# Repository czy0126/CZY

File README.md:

# CZY — 48 V → 约 2 V 薄型固定变比 DCX

**D1 当前设计目标：** 约 24:1 固定比、100 A 输出目标、整机高度 ≤16 mm；成本暂不限制。D2 的 120 A 与 D3 的 ≤10 mm 均后置，保护、绝缘、载流与制造签核不可省。

> **当前研发分支：[`feat/d1-fab-package`](https://github.com/czy0126/CZY/tree/feat/d1-fab-package)。默认 `main` 仍是历史快照。当前 D1 为 `NOT_FOR_FAB`；真实样机尚未获得投板或额定许可。**

## 从这里开始（不用翻旧审核报告）

1. **[D1 当前交接面板](docs/D1_CURRENT.md)**：唯一当前可编辑 G1 原生 PCB、已发生的 ECO、三条并行任务及下一次操作/验收。
2. **[D1 已决事项与重开条件](docs/D1_DECISIONS.md)**：R8/R6、Lr XY、九根布线预检、100 A 铜路等已经确认的边界；禁止重复审查同一证据。
3. **[第49章：D1 G1→G2→G3 交付合同](docs/D1_EXECUTION_KIT/49_D1主功率板PCB唯一执行计划_2026-11-09.md)**：阶段目标、冻结条件与实际制造要求；其 11/9 日期快照不覆盖当前 G1 读回。
4. **[历史技术资料索引](docs/D1_REFERENCE_INDEX.md)**：资料在哪里、哪些只作参考。原 README 的长篇历史更新已[归档](docs/archive/README_D1_branch_before_single_entry_2026-11-10.md)，保留所有技术原文和链接。

**唯一任务入口：** [Issue #4 总交付](https://github.com/czy0126/CZY/issues/4)，以及 [#9 原生 PCB/器件](https://github.com/czy0126/CZY/issues/9)、[#12 磁件与接口](https://github.com/czy0126/CZY/issues/12)、[#36 D0 保护](https://github.com/czy0126/CZY/issues/36)。**同时最多 A/B/C 三个工程工作包**；不为“再次审核/继续优化”新建总计划。

## 实际应该先做什么

**A 线优先：** 9条控制小信号增量已完成原生重开验收，未连接206→199，Physical 0、Netlist仍1；见[同CAD审核回执](hardware/dcx_main/g1/lr_signal_review_report.json)。下一步处理原生Import Changes逐位号差异、实体Cout和100 A两极铜路，不重复重画已有短线。

```powershell
python -m pytest tools/test_g1_copper_coverage.py tools/test_g1_driver_route_plan.py -q
```

上述测试是回归检查，不替代原生DRC；本轮信号候选及失败回执全部保留，尚待随本轮提交提升基线。B（真实 Maxwell/实体 PAD）与 C（D0 真实关断）并行，不得以模拟或脚本绿色替代实际硬件证据。

**工程和开发规则：** [`CLAUDE.md`](CLAUDE.md) · [`docs/agent/EDA.md`](docs/agent/EDA.md) · [PR 模板](.github/PULL_REQUEST_TEMPLATE.md)。任何 PR 应说明真实产物的**改动前后、原始证据和下一次实际交付**。仅更换“最新计划”标题或重复风险总结不算里程碑。

**制造许可唯一来源：** [`hardware/dcx_main/d1_fabrication_gate.json`](hardware/dcx_main/d1_fabrication_gate.json) 及其相同 CAD 修订版的独立审核证据；历史 JSON 不能混用为 G1 的签核。

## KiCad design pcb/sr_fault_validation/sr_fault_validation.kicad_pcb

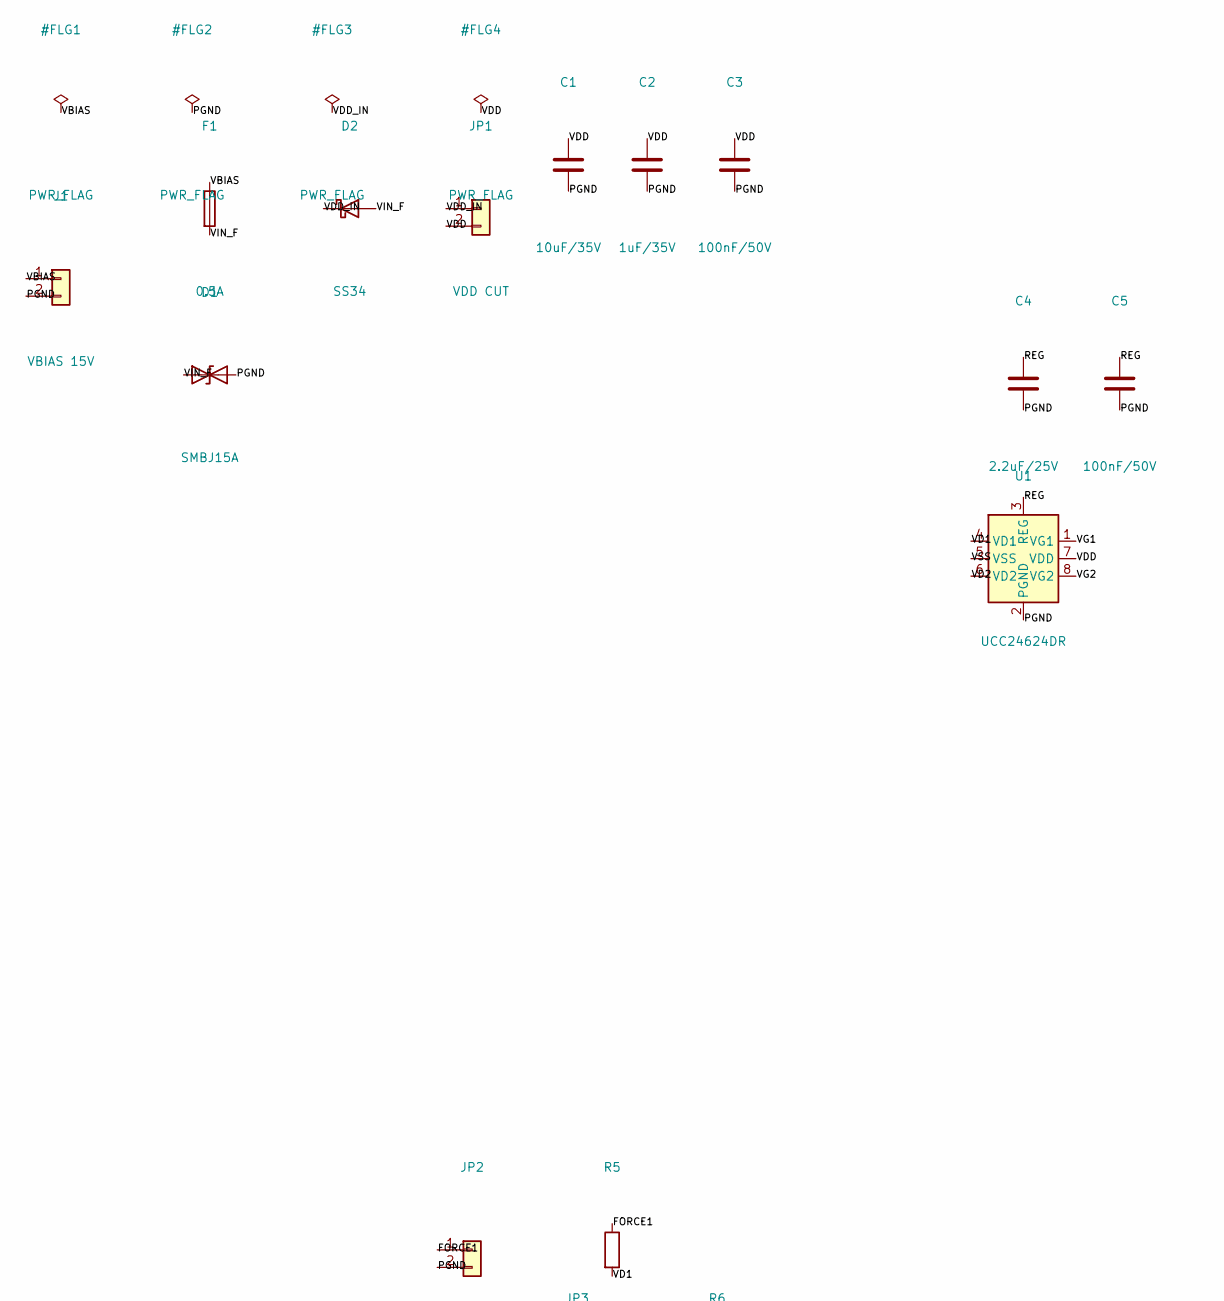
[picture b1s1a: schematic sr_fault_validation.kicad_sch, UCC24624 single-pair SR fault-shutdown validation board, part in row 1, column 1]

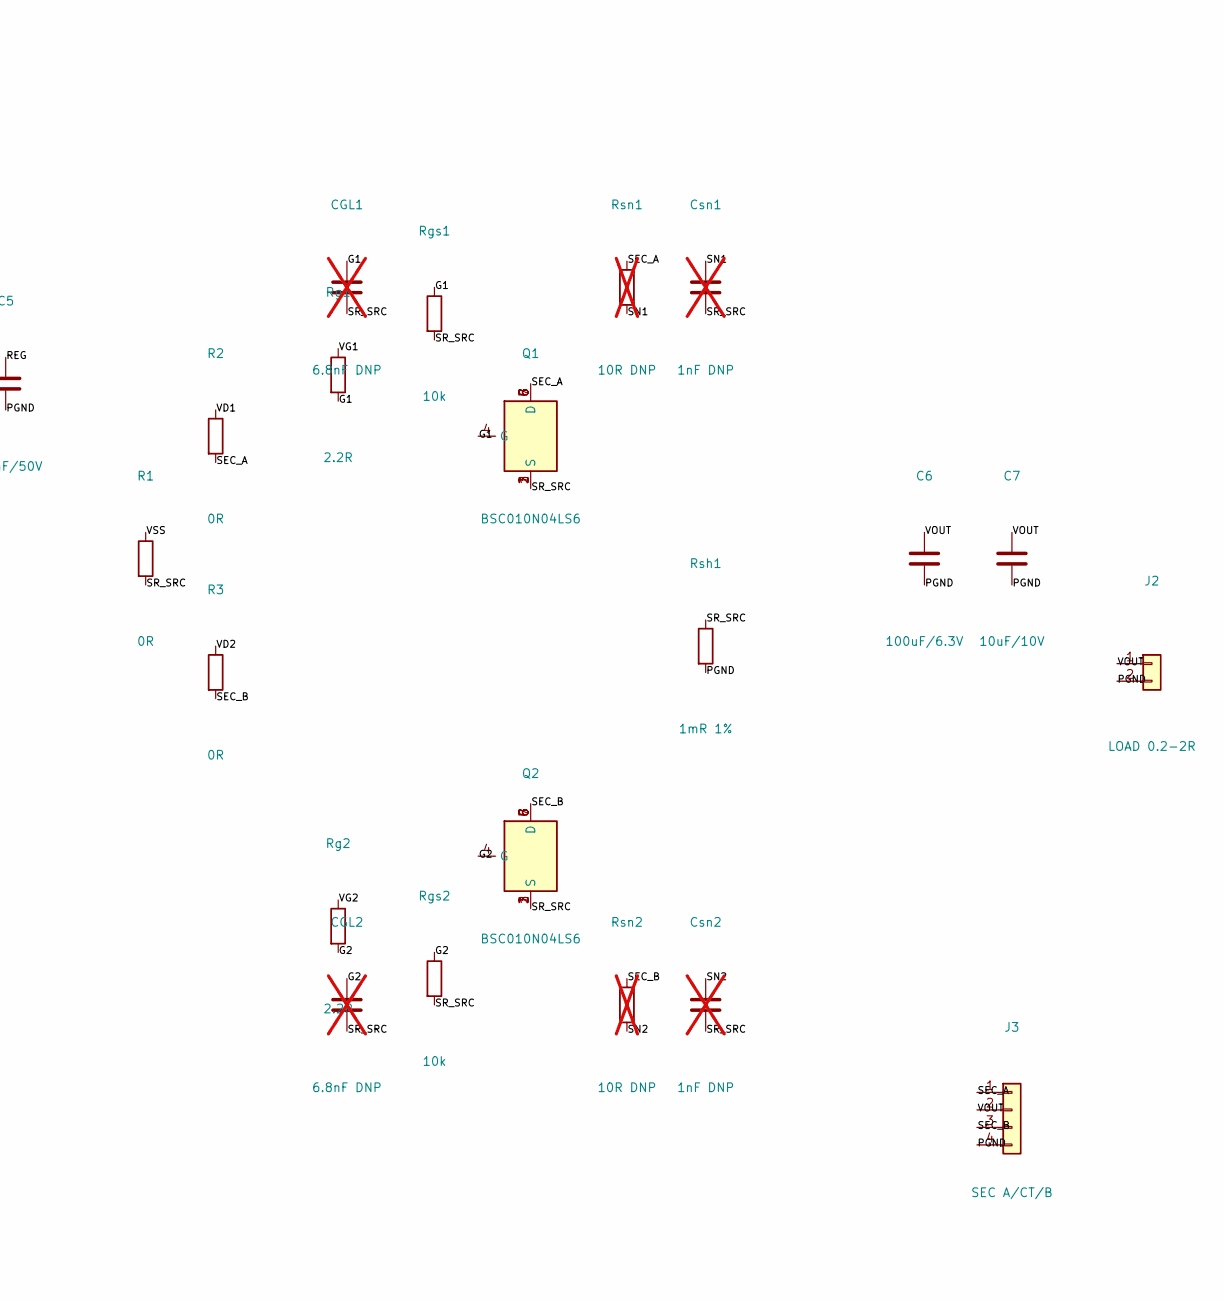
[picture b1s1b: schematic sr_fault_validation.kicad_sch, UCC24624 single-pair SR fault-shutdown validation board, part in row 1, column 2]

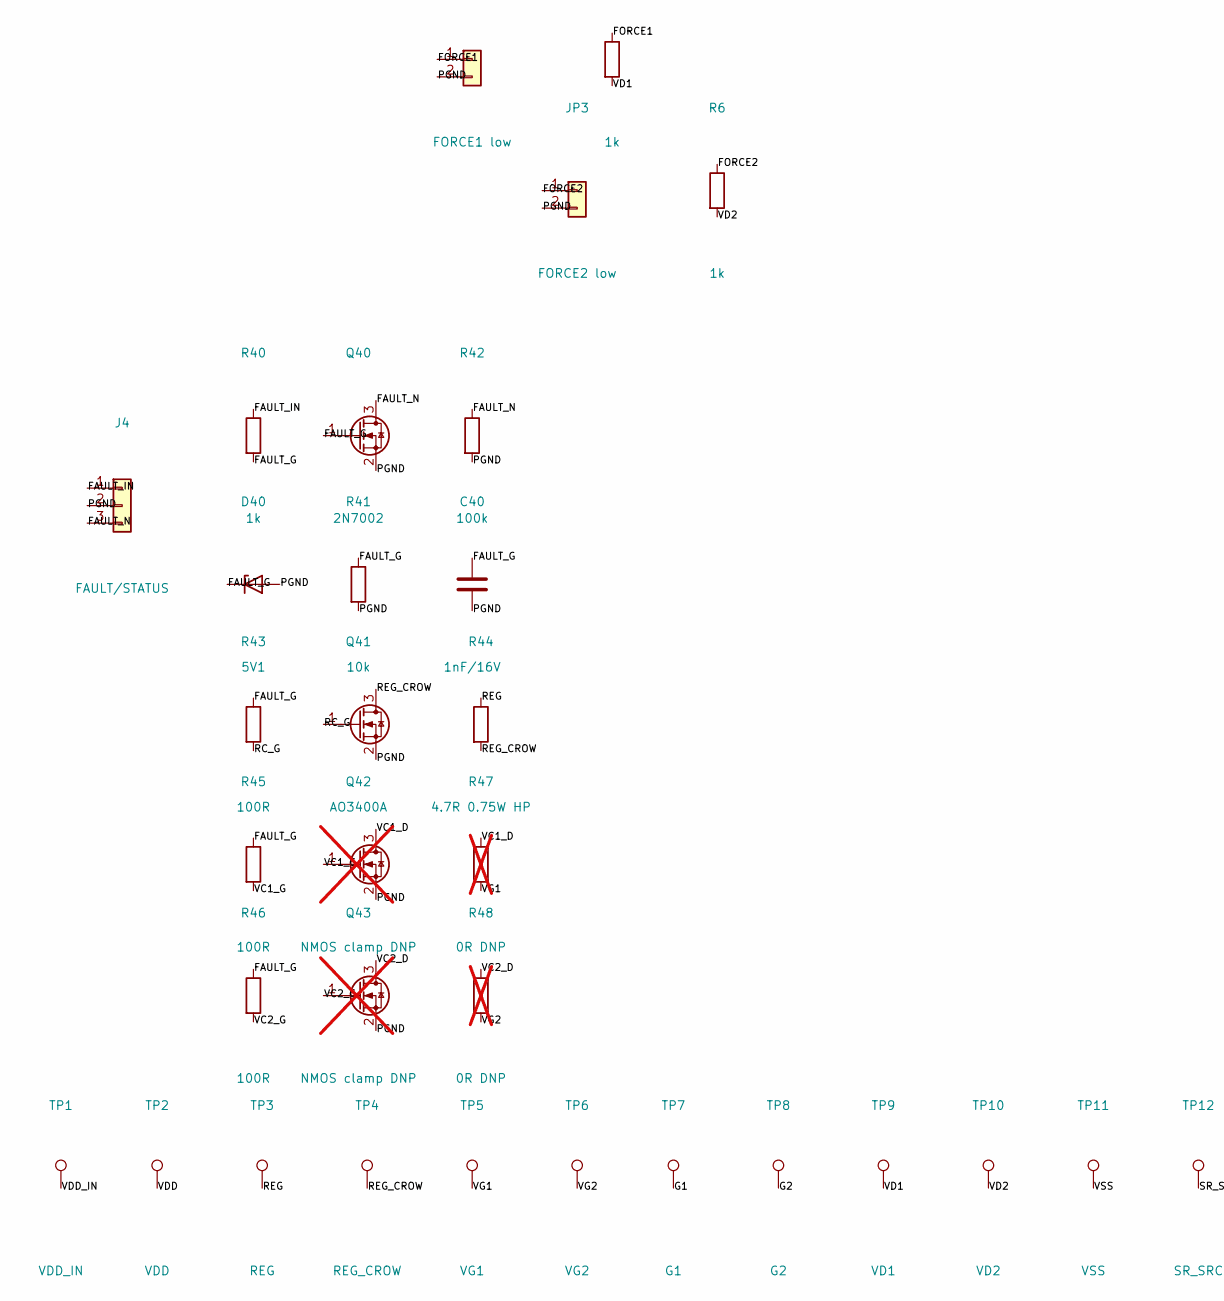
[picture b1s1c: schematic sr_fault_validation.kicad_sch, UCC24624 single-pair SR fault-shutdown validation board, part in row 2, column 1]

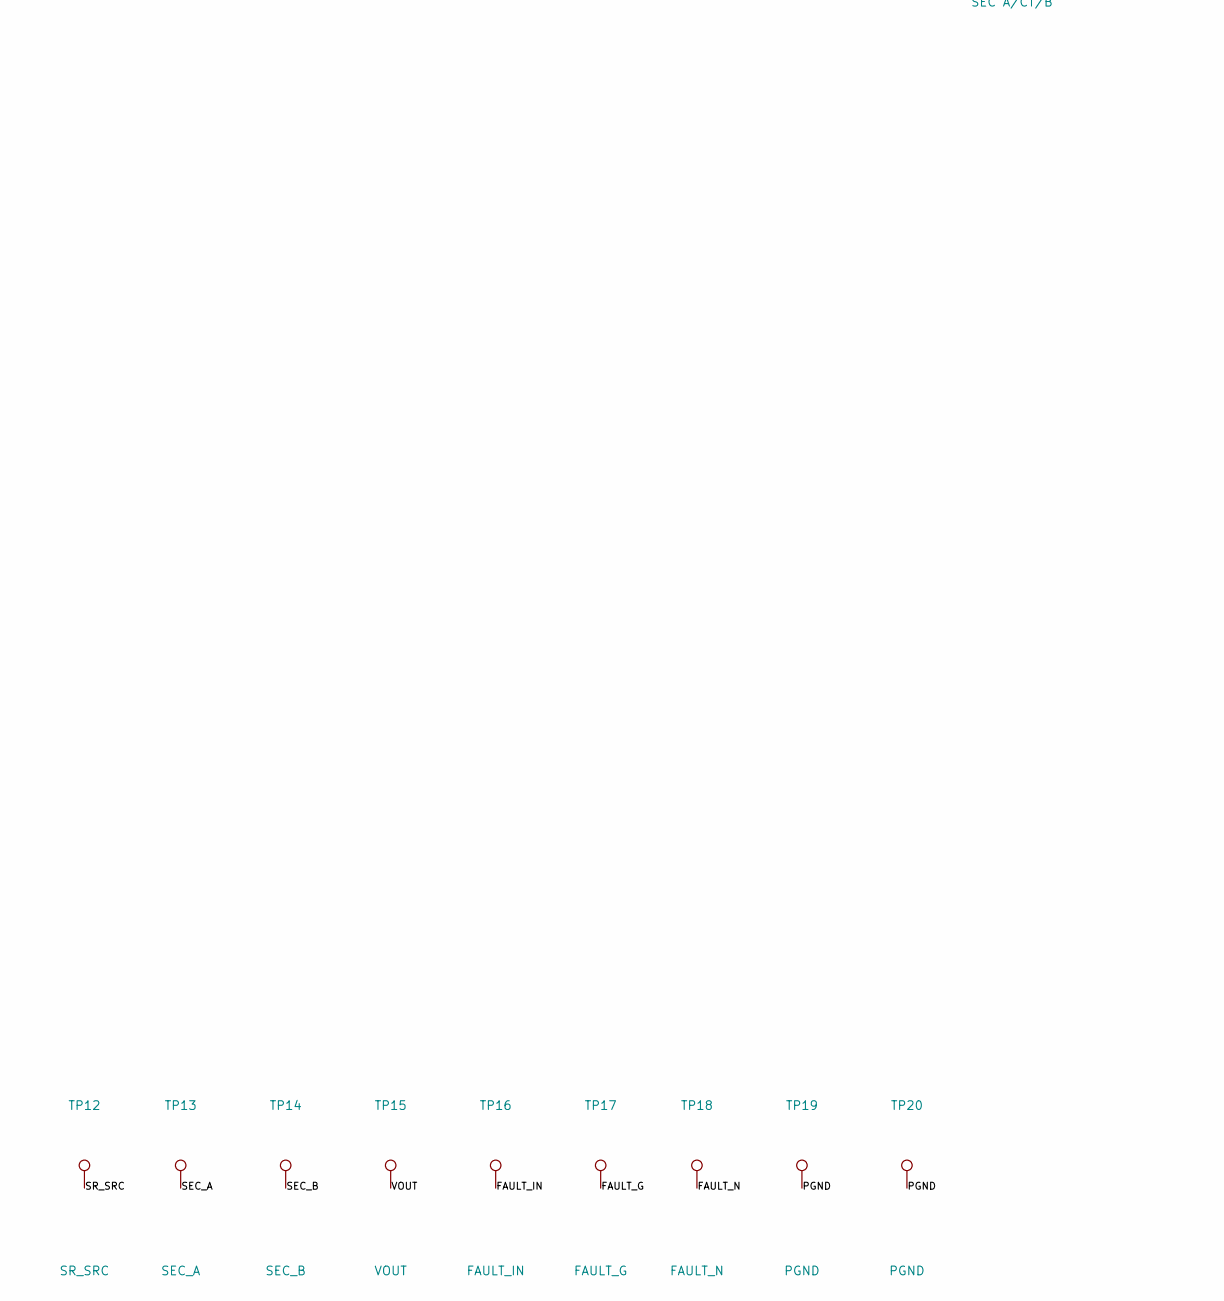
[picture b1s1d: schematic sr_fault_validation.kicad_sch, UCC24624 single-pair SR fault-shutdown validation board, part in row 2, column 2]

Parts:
C1: 10uF/35V; C_1210_3225Metric
C2: 1uF/35V; C_0805_2012Metric
C3, C5: 100nF/50V; C_0603_1608Metric
C4: 2.2uF/25V; C_1206_3216Metric
C6: 100uF/6.3V; C_1210_3225Metric
C7: 10uF/10V; C_0805_2012Metric
C40: 1nF/16V; C_0603_1608Metric
CGL1, CGL2: 6.8nF DNP; C_0603_1608Metric; not fitted
Csn1, Csn2: 1nF DNP; C_0603_1608Metric; not fitted
D1: SMBJ15A; D_SMB
D2: SS34; D_SMA
D40: 5V1; D_SOD-123
F1: 0.5A; Fuse_1206_3216Metric
J1: VBIAS 15V; TerminalBlock_MaiXu_MX126-5.0-02P_1x02_P5.00mm
J2: LOAD 0.2-2R; TerminalBlock_MaiXu_MX126-5.0-02P_1x02_P5.00mm
J3: SEC A/CT/B; TerminalBlock_MaiXu_MX126-5.0-04P_1x04_P5.00mm
J4: FAULT/STATUS; PinHeader_1x03_P2.54mm_Vertical
JP1: VDD CUT; PinHeader_1x02_P2.54mm_Vertical
JP2: FORCE1 low; PinHeader_1x02_P2.54mm_Vertical
JP3: FORCE2 low; PinHeader_1x02_P2.54mm_Vertical
Q1, Q2: BSC010N04LS6
Q40: 2N7002; SOT-23
Q41: AO3400A; SOT-23
Q42, Q43: NMOS clamp DNP; SOT-23; not fitted
R1: 0R; R_0805_2012Metric
R2, R3: 0R; R_0603_1608Metric
R5, R6, R40: 1k; R_0603_1608Metric
R41: 10k; R_0603_1608Metric
R42: 100k; R_0603_1608Metric
R43, R45, R46: 100R; R_0603_1608Metric
R44: 4.7R 0.75W HP; R_1206_3216Metric
R47, R48: 0R DNP; R_0805_2012Metric; not fitted
Rg1, Rg2: 2.2R; R_0805_2012Metric
Rgs1, Rgs2: 10k; R_0603_1608Metric
Rsh1: 1mR 1%; R_2512_6332Metric
Rsn1, Rsn2: 10R DNP; R_0603_1608Metric; not fitted
TP1: VDD_IN; TestPoint_Pad_D1.0mm
TP2: VDD; TestPoint_Pad_D1.0mm
TP3: REG; TestPoint_Pad_D1.0mm
TP4: REG_CROW; TestPoint_Pad_D1.0mm
TP5: VG1; TestPoint_Pad_D1.0mm
TP6: VG2; TestPoint_Pad_D1.0mm
TP7: G1; TestPoint_Pad_D1.0mm
TP8: G2; TestPoint_Pad_D1.0mm
TP9: VD1; TestPoint_Pad_D1.0mm
TP10: VD2; TestPoint_Pad_D1.0mm
TP11: VSS; TestPoint_Pad_D1.0mm
TP12: SR_SRC; TestPoint_Pad_D1.0mm
TP13: SEC_A; TestPoint_Pad_D1.0mm
TP14: SEC_B; TestPoint_Pad_D1.0mm
TP15: VOUT; TestPoint_Pad_D1.0mm
TP16: FAULT_IN; TestPoint_Pad_D1.0mm
TP17: FAULT_G; TestPoint_Pad_D1.0mm
TP18: FAULT_N; TestPoint_Pad_D1.0mm
TP19, TP20: PGND; TestPoint_Pad_D1.0mm
U1: UCC24624DR; SOIC-8_3.9x4.9mm_P1.27mm

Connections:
FAULT_G: C40.1, D40.1 (K), Q40.1 (G), R40.2, R41.1, R43.1, R45.1, R46.1, TP17.1
FAULT_IN: J4.1, R40.1, TP16.1
FAULT_N: J4.3, Q40.3 (D), R42.1, TP18.1
FORCE1: JP2.1, R5.1
FORCE2: JP3.1, R6.1
G1: CGL1.1, Q1.4 (G), Rg1.2, Rgs1.1, TP7.1
G2: CGL2.1, Q2.4 (G), Rg2.2, Rgs2.1, TP8.1
PGND: C1.2, C2.2, C3.2, C4.2, C5.2, C6.2, C7.2, C40.2, D1.2 (A2), D40.2 (A), J1.2, J2.2, J3.4, J4.2, JP2.2, JP3.2, Q40.2 (S), Q41.2 (S), Q42.2 (S), Q43.2 (S), R41.2, R42.2, Rsh1.2, TP19.1, TP20.1, U1.2 (PGND)
RC_G: Q41.1 (G), R43.2
REG: C4.1, C5.1, R44.1, TP3.1, U1.3 (REG)
REG_CROW: Q41.3 (D), R44.2, TP4.1
SEC_A: J3.1, Q1.5 (D), Q1.6 (D), Q1.7 (D), Q1.8 (D), R2.2, Rsn1.1, TP13.1
SEC_B: J3.3, Q2.5 (D), Q2.6 (D), Q2.7 (D), Q2.8 (D), R3.2, Rsn2.1, TP14.1
SN1: Csn1.1, Rsn1.2
SN2: Csn2.1, Rsn2.2
SR_SRC: CGL1.2, CGL2.2, Csn1.2, Csn2.2, Q1.1 (S), Q1.2 (S), Q1.3 (S), Q2.1 (S), Q2.2 (S), Q2.3 (S), R1.2, Rgs1.2, Rgs2.2, Rsh1.1, TP12.1
VBIAS: F1.1, J1.1
VC1_D: Q42.3 (D), R47.1
VC1_G: Q42.1 (G), R45.2
VC2_D: Q43.3 (D), R48.1
VC2_G: Q43.1 (G), R46.2
VD1: R2.1, R5.2, TP9.1, U1.4 (VD1)
VD2: R3.1, R6.2, TP10.1, U1.6 (VD2)
VDD: C1.1, C2.1, C3.1, JP1.2, TP2.1, U1.7 (VDD)
VDD_IN: D2.1 (K), JP1.1, TP1.1
VG1: R47.2, Rg1.1, TP5.1, U1.1 (VG1)
VG2: R48.2, Rg2.1, TP6.1, U1.8 (VG2)
VIN_F: D1.1 (A1), D2.2 (A), F1.2
VOUT: C6.1, C7.1, J2.1, J3.2, TP15.1
VSS: R1.1, TP11.1, U1.5 (VSS)

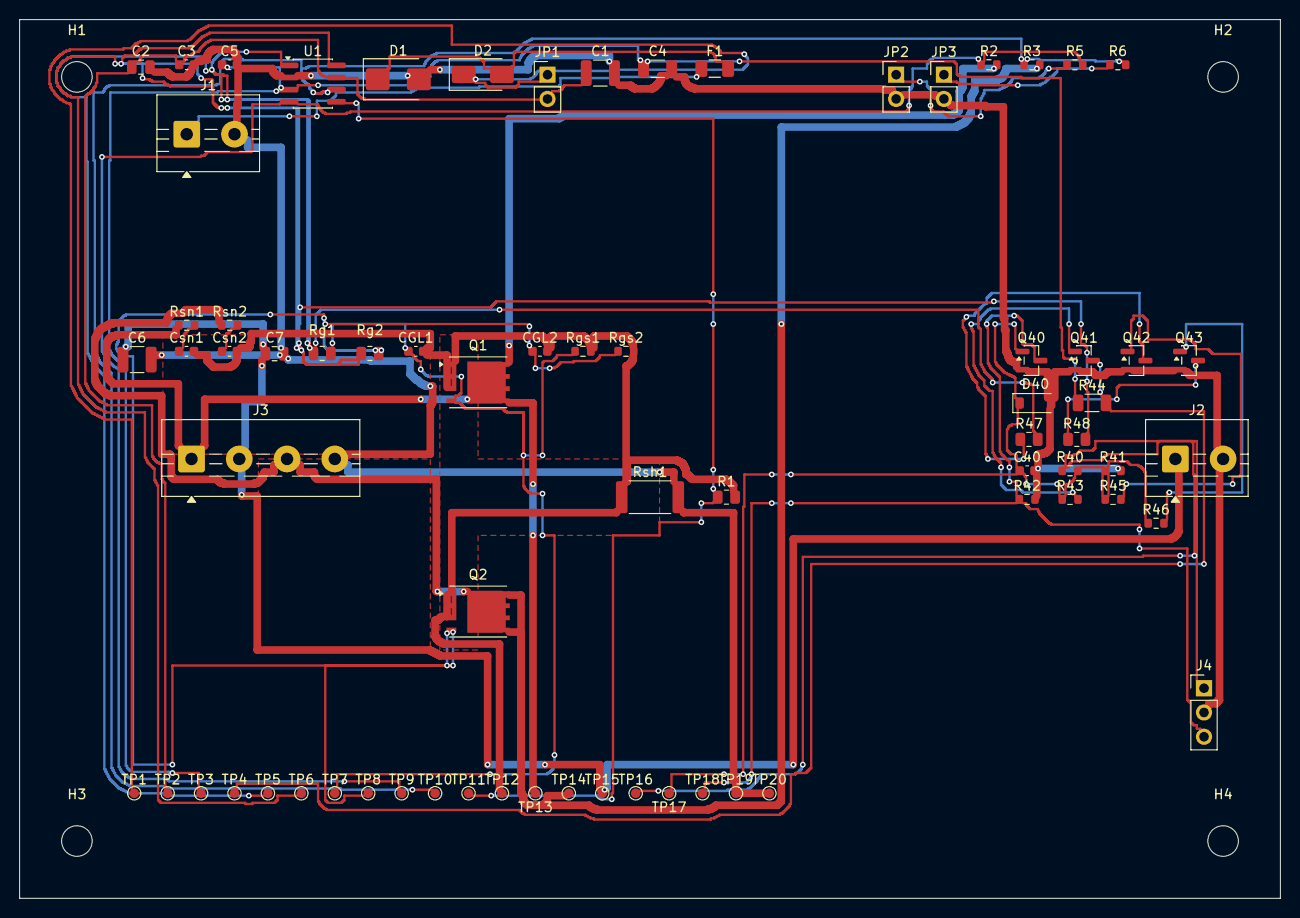
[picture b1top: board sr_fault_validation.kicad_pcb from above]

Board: 2 copper layers, 132.0 x 92.0 mm, 75 parts (0 on the bottom side), 30 nets.

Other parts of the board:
H1, H2, H3, H4: MountingHole_3.2mm_M3

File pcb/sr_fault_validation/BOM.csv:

Reference,Value,Footprint,Rating,Note,DNP,MPN,MPN_Source,LCSC,Qty
J1,VBIAS 15V,TerminalBlock:TerminalBlock_MaiXu_MX126-5.0-02P_1x02_P5.00mm,"15 V, 0.5 A",bias input; polarity marked on the silk,,,TO_SELECT,,1
F1,0.5A,Fuse:Fuse_1206_3216Metric,0.5 A,bias fuse,,,TO_SELECT,,1
D1,SMBJ15A,Diode_SMD:D_SMB,15 V standoff,bias TVS,,,TO_SELECT,,1
D2,SS34,Diode_SMD:D_SMA,40 V 3 A,reverse-polarity block; pin 1 is the cathode,,,TO_SELECT,,1
JP1,VDD CUT,Connector_PinHeader_2.54mm:PinHeader_1x02_P2.54mm_Vertical,,shunt fitted = VDD connected; remove to test a VDD-only cut,,,TO_SELECT,,1
C1,10uF/35V,Capacitor_SMD:C_1210_3225Metric,35 V X7R,,,,TO_SELECT,,1
C2,1uF/35V,Capacitor_SMD:C_0805_2012Metric,35 V X7R,,,,TO_SELECT,,1
C3,100nF/50V,Capacitor_SMD:C_0603_1608Metric,50 V X7R,at pin 7,,,TO_SELECT,,1
U1,UCC24624DR,Package_SO:SOIC-8_3.9x4.9mm_P1.27mm,230 V VD pins,"SR controller, SOIC-8",,UCC24624DR,references/datasheets/ucc24624.txt,,1
C4,2.2uF/25V,Capacitor_SMD:C_1206_3216Metric,25 V X7R,"REG bypass, <=1 cm from pin 3",,,TO_SELECT,,1
C5,100nF/50V,Capacitor_SMD:C_0603_1608Metric,50 V X7R,REG HF bypass,,,TO_SELECT,,1
R1,0R,Resistor_SMD:R_0805_2012Metric,<=212 R option,Roffset: VTHOFF = 10.5 mV + 330 uA * R; 0R keeps the datasheet value,,,TO_SELECT,,1
R2,0R,Resistor_SMD:R_0603_1608Metric,100 R option,VD1 series link; 100R only if drain ringing demands it,,,TO_SELECT,,1
R3,0R,Resistor_SMD:R_0603_1608Metric,100 R option,VD2 series link,,,TO_SELECT,,1
Q1,BSC010N04LS6,dcx:BSC010N04LS6,40 V 1.0 mR,SR1; source Kelvin to VSS,,BSC010N04LS6,references/datasheets/bsc010n04ls6.txt,,1
Q2,BSC010N04LS6,dcx:BSC010N04LS6,40 V 1.0 mR,SR2; source Kelvin to VSS,,BSC010N04LS6,references/datasheets/bsc010n04ls6.txt,,1
Rg1,2.2R,Resistor_SMD:R_0805_2012Metric,1/8 W,"gate resistor, main-board value",,,TO_SELECT,,1
Rg2,2.2R,Resistor_SMD:R_0805_2012Metric,1/8 W,"gate resistor, main-board value",,,TO_SELECT,,1
Rgs1,10k,Resistor_SMD:R_0603_1608Metric,1/10 W,gate-source pulldown,,,TO_SELECT,,1
Rgs2,10k,Resistor_SMD:R_0603_1608Metric,1/10 W,gate-source pulldown,,,TO_SELECT,,1
CGL1,6.8nF DNP,Capacitor_SMD:C_0603_1608Metric,50 V,gate-load test,yes,,TO_SELECT,,1
CGL2,6.8nF DNP,Capacitor_SMD:C_0603_1608Metric,50 V,gate-load test,yes,,TO_SELECT,,1
Rsh1,1mR 1%,Resistor_SMD:R_2512_6332Metric,2 W,return current sense; 10 A -> 10 mV,,,TO_SELECT,,1
Rsn1,10R DNP,Resistor_SMD:R_0603_1608Metric,1/10 W,RC snubber,yes,,TO_SELECT,,1
Csn1,1nF DNP,Capacitor_SMD:C_0603_1608Metric,50 V,RC snubber,yes,,TO_SELECT,,1
Rsn2,10R DNP,Resistor_SMD:R_0603_1608Metric,1/10 W,RC snubber,yes,,TO_SELECT,,1
Csn2,1nF DNP,Capacitor_SMD:C_0603_1608Metric,50 V,RC snubber,yes,,TO_SELECT,,1
J3,SEC A/CT/B,TerminalBlock:TerminalBlock_MaiXu_MX126-5.0-04P_1x04_P5.00mm,"20 V peak, 10 A",isolated low-voltage centre-tapped source,,,TO_SELECT,,1
C6,100uF/6.3V,Capacitor_SMD:C_1210_3225Metric,6.3 V X5R,,,,TO_SELECT,,1
C7,10uF/10V,Capacitor_SMD:C_0805_2012Metric,10 V X7R,,,,TO_SELECT,,1
J2,LOAD 0.2-2R,TerminalBlock:TerminalBlock_MaiXu_MX126-5.0-02P_1x02_P5.00mm,2 A max,load / electronic load,,,TO_SELECT,,1
R5,1k,Resistor_SMD:R_0603_1608Metric,1/10 W,VD1 injection,,,TO_SELECT,,1
R6,1k,Resistor_SMD:R_0603_1608Metric,1/10 W,VD2 injection,,,TO_SELECT,,1
JP2,FORCE1 low,Connector_PinHeader_2.54mm:PinHeader_1x02_P2.54mm_Vertical,,shunt = force VD1 low,,,TO_SELECT,,1
JP3,FORCE2 low,Connector_PinHeader_2.54mm:PinHeader_1x02_P2.54mm_Vertical,,shunt = force VD2 low,,,TO_SELECT,,1
J4,FAULT/STATUS,Connector_PinHeader_2.54mm:PinHeader_1x03_P2.54mm_Vertical,"3.3/5 V CMOS or open-drain, active high","pin 1 = fault request, pin 3 = open-drain status",,,TO_SELECT,,1
R40,1k,Resistor_SMD:R_0603_1608Metric,1/10 W,series limit into the clamp,,,TO_SELECT,,1
D40,5V1,Diode_SMD:D_SOD-123,5.1 V,"input clamp; two-pad land so the cathode (pad 1, the banded end) actually reaches FAULT_G -- an SOT-23 land left pad 3, which is where a BZX84 puts its cathode, as spare copper.  MPN TO_SELECT: no 5.1 V zener datasheet is in the repository",,,TO_SELECT,,1
R41,10k,Resistor_SMD:R_0603_1608Metric,1/10 W,default = no fault (fail-open input); 10k * 1nF = 10 us input filter,,,TO_SELECT,,1
C40,1nF/16V,Capacitor_SMD:C_0603_1608Metric,16 V X7R,10 us; a 1 ms debounce would dominate every other delay,,,TO_SELECT,,1
Q40,2N7002,Package_TO_SOT_SMD:SOT-23,60 V,open-drain status: low while the fault is asserted,,2N7002LT1G,references/datasheets/2n7002lt1g_onsemi_oem_parameters.txt,,1
R42,100k,Resistor_SMD:R_0603_1608Metric,1/10 W,status default low; the external pull-up sees this 100k to PGND,,,TO_SELECT,,1
R43,100R,Resistor_SMD:R_0603_1608Metric,1/10 W,crowbar gate resistor,,,TO_SELECT,,1
Q41,AO3400A,Package_TO_SOT_SMD:SOT-23,"30 V, 5.7 A, IDM 30 A","REG crowbar; 3.0 V gate from a 3.3 V harness, Rds(on) <= 0.048 ohm at 2.5 V VGS (max, 25 C); absorbs 0.001 mJ per event; selected, not qualified (see report q41_selection)",,AO3400A,references/datasheets/ao3400a.txt,,1
R44,4.7R 0.75W HP,Resistor_SMD:R_1206_3216Metric,0.75 W conditional; pulse screen,"sets the discharge tau with Q41; 0.123 mJ / 25.2 W peak per event (4.9 us equivalent), CRCW-HP conditional pulse screen; hardware qualification UNVERIFIED",,CRCW12064R70FKEAHP,references/datasheets/vishay_crcwhpe3_20260317.pdf,,1
R45,100R,Resistor_SMD:R_0603_1608Metric,1/10 W,VG1 clamp gate resistor,,,TO_SELECT,,1
Q42,NMOS clamp DNP,Package_TO_SOT_SMD:SOT-23,30 V,optional VG1 clamp; contention test only,yes,,TO_SELECT,,1
R47,0R DNP,Resistor_SMD:R_0805_2012Metric,1/4 W,clamp link: fitting this removes U1's ability to hold VG1 high,yes,,TO_SELECT,,1
R46,100R,Resistor_SMD:R_0603_1608Metric,1/10 W,VG2 clamp gate resistor,,,TO_SELECT,,1
Q43,NMOS clamp DNP,Package_TO_SOT_SMD:SOT-23,30 V,optional VG2 clamp; contention test only,yes,,TO_SELECT,,1
R48,0R DNP,Resistor_SMD:R_0805_2012Metric,1/4 W,clamp link,yes,,TO_SELECT,,1
TP1,VDD_IN,TestPoint:TestPoint_Pad_D1.0mm,1 mm pad,scope probe / Kelvin point,,,TO_SELECT,,1
TP2,VDD,TestPoint:TestPoint_Pad_D1.0mm,1 mm pad,scope probe / Kelvin point,,,TO_SELECT,,1
TP3,REG,TestPoint:TestPoint_Pad_D1.0mm,1 mm pad,scope probe / Kelvin point,,,TO_SELECT,,1
TP4,REG_CROW,TestPoint:TestPoint_Pad_D1.0mm,1 mm pad,scope probe / Kelvin point,,,TO_SELECT,,1
TP5,VG1,TestPoint:TestPoint_Pad_D1.0mm,1 mm pad,scope probe / Kelvin point,,,TO_SELECT,,1
TP6,VG2,TestPoint:TestPoint_Pad_D1.0mm,1 mm pad,scope probe / Kelvin point,,,TO_SELECT,,1
TP7,G1,TestPoint:TestPoint_Pad_D1.0mm,1 mm pad,scope probe / Kelvin point,,,TO_SELECT,,1
TP8,G2,TestPoint:TestPoint_Pad_D1.0mm,1 mm pad,scope probe / Kelvin point,,,TO_SELECT,,1
TP9,VD1,TestPoint:TestPoint_Pad_D1.0mm,1 mm pad,scope probe / Kelvin point,,,TO_SELECT,,1
TP10,VD2,TestPoint:TestPoint_Pad_D1.0mm,1 mm pad,scope probe / Kelvin point,,,TO_SELECT,,1
TP11,VSS,TestPoint:TestPoint_Pad_D1.0mm,1 mm pad,scope probe / Kelvin point,,,TO_SELECT,,1
TP12,SR_SRC,TestPoint:TestPoint_Pad_D1.0mm,1 mm pad,scope probe / Kelvin point,,,TO_SELECT,,1
TP13,SEC_A,TestPoint:TestPoint_Pad_D1.0mm,1 mm pad,scope probe / Kelvin point,,,TO_SELECT,,1
TP14,SEC_B,TestPoint:TestPoint_Pad_D1.0mm,1 mm pad,scope probe / Kelvin point,,,TO_SELECT,,1
TP15,VOUT,TestPoint:TestPoint_Pad_D1.0mm,1 mm pad,scope probe / Kelvin point,,,TO_SELECT,,1
TP16,FAULT_IN,TestPoint:TestPoint_Pad_D1.0mm,1 mm pad,scope probe / Kelvin point,,,TO_SELECT,,1
TP17,FAULT_G,TestPoint:TestPoint_Pad_D1.0mm,1 mm pad,scope probe / Kelvin point,,,TO_SELECT,,1
TP18,FAULT_N,TestPoint:TestPoint_Pad_D1.0mm,1 mm pad,scope probe / Kelvin point,,,TO_SELECT,,1
TP19,PGND,TestPoint:TestPoint_Pad_D1.0mm,1 mm pad,scope probe / Kelvin point,,,TO_SELECT,,1
TP20,PGND,TestPoint:TestPoint_Pad_D1.0mm,1 mm pad,scope probe / Kelvin point,,,TO_SELECT,,1

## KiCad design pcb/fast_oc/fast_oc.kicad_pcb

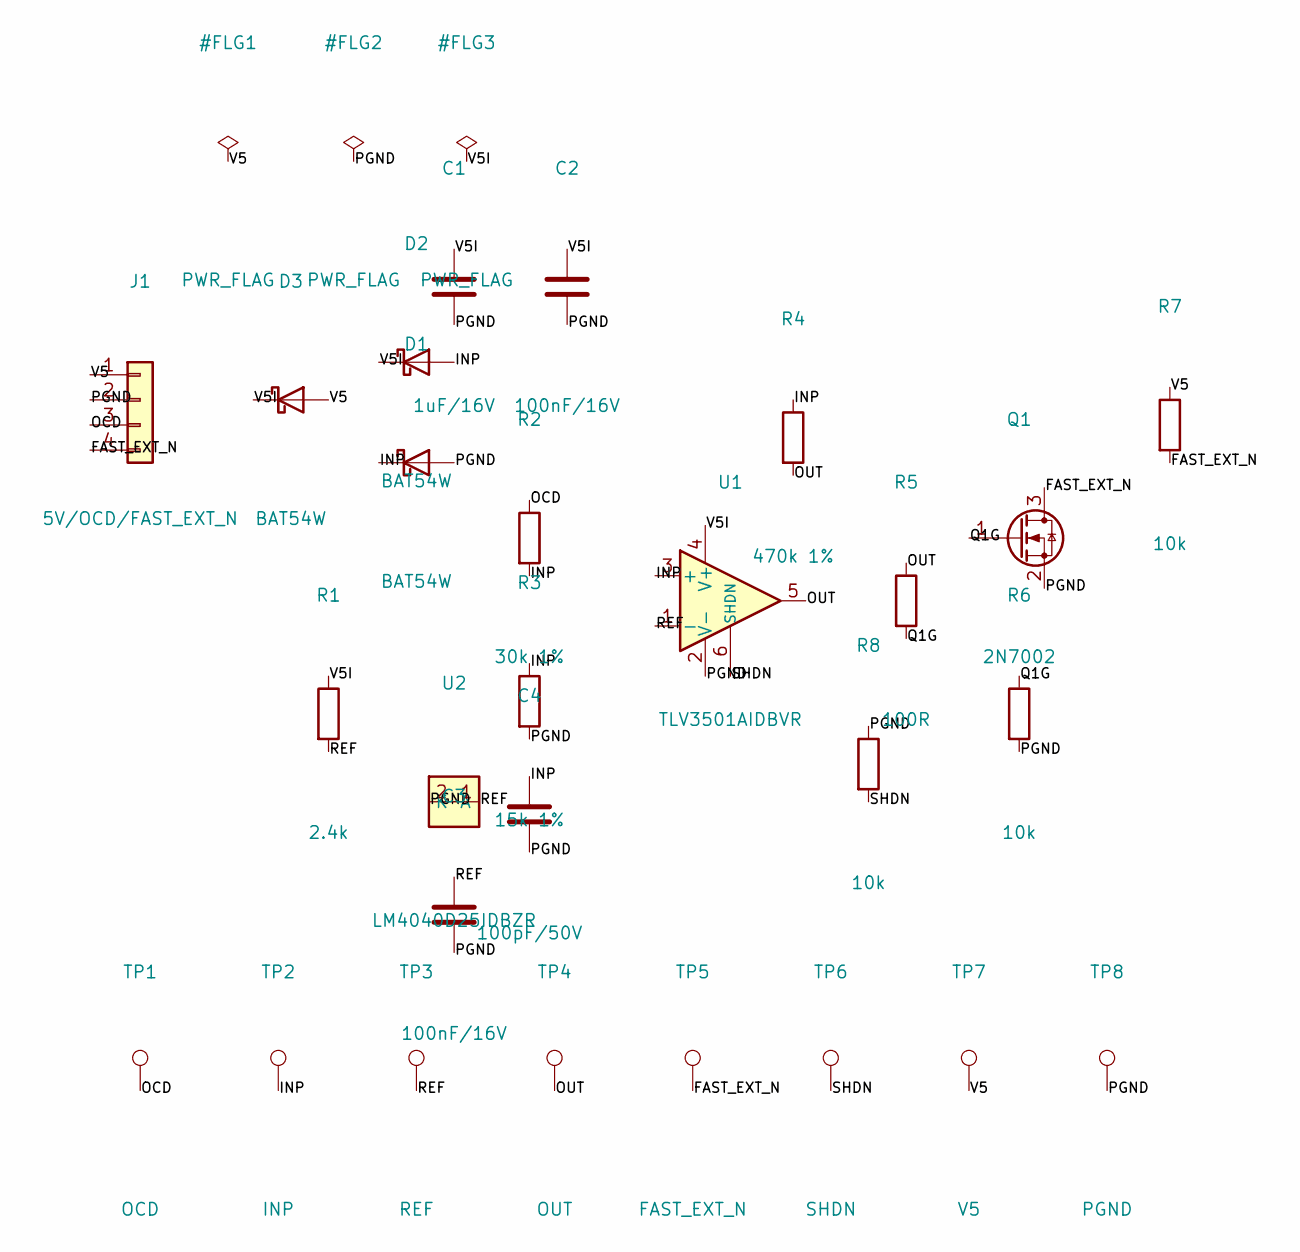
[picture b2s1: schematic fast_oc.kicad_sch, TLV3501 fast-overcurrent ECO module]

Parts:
C1: 1uF/16V; C_0603_1608Metric
C2, C3: 100nF/16V; C_0603_1608Metric
C4: 100pF/50V; C_0603_1608Metric
D1, D2, D3: BAT54W; D_SOD-123
J1: 5V/OCD/FAST_EXT_N; PinHeader_1x04_P2.54mm_Vertical
Q1: 2N7002; SOT-23
R1: 2.4k; R_0603_1608Metric
R2: 30k 1%; R_0603_1608Metric
R3: 15k 1%; R_0603_1608Metric
R4: 470k 1%; R_0603_1608Metric
R5: 100R; R_0603_1608Metric
R6, R7, R8: 10k; R_0603_1608Metric
TP1: OCD; TestPoint_Pad_D1.0mm
TP2: INP; TestPoint_Pad_D1.0mm
TP3: REF; TestPoint_Pad_D1.0mm
TP4: OUT; TestPoint_Pad_D1.0mm
TP5: FAST_EXT_N; TestPoint_Pad_D1.0mm
TP6: SHDN; TestPoint_Pad_D1.0mm
TP7: V5; TestPoint_Pad_D1.0mm
TP8: PGND; TestPoint_Pad_D1.0mm
U1: TLV3501AIDBVR; SOT-23-6
U2: LM4040D25IDBZR; SOT-23

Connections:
FAST_EXT_N: J1.4, Q1.3 (D), R7.2, TP5.1
INP: C4.1, D1.1 (K), D2.2 (A), R2.2, R3.1, R4.1, TP2.1, U1.3 (+)
OCD: J1.3, R2.1, TP1.1
OUT: R4.2, R5.1, TP4.1, U1.5
PGND: C1.2, C2.2, C3.2, C4.2, D1.2 (A), J1.2, Q1.2 (S), R3.2, R6.2, R8.1, TP8.1, U1.2 (V-), U2.2 (A)
Q1G: Q1.1 (G), R5.2, R6.1
REF: C3.1, R1.2, TP3.1, U1.1 (-), U2.1 (K)
SHDN: R8.2, TP6.1, U1.6 (SHDN)
V5: D3.2 (A), J1.1, R7.1, TP7.1
V5I: C1.1, C2.1, D2.1 (K), D3.1 (K), R1.1, U1.4 (V+)

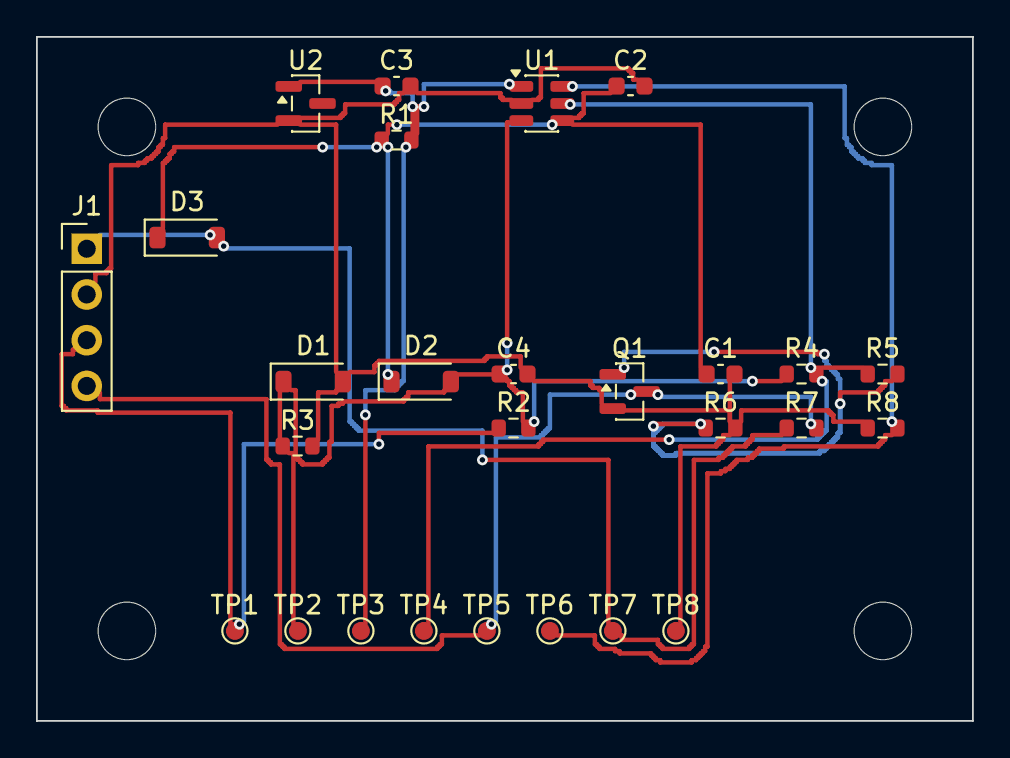
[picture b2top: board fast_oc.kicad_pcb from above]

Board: 2 copper layers, 52.0 x 38.0 mm, 31 parts (0 on the bottom side), 10 nets.

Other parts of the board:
H1, H2, H3, H4: MountingHole_3.2mm_M3
